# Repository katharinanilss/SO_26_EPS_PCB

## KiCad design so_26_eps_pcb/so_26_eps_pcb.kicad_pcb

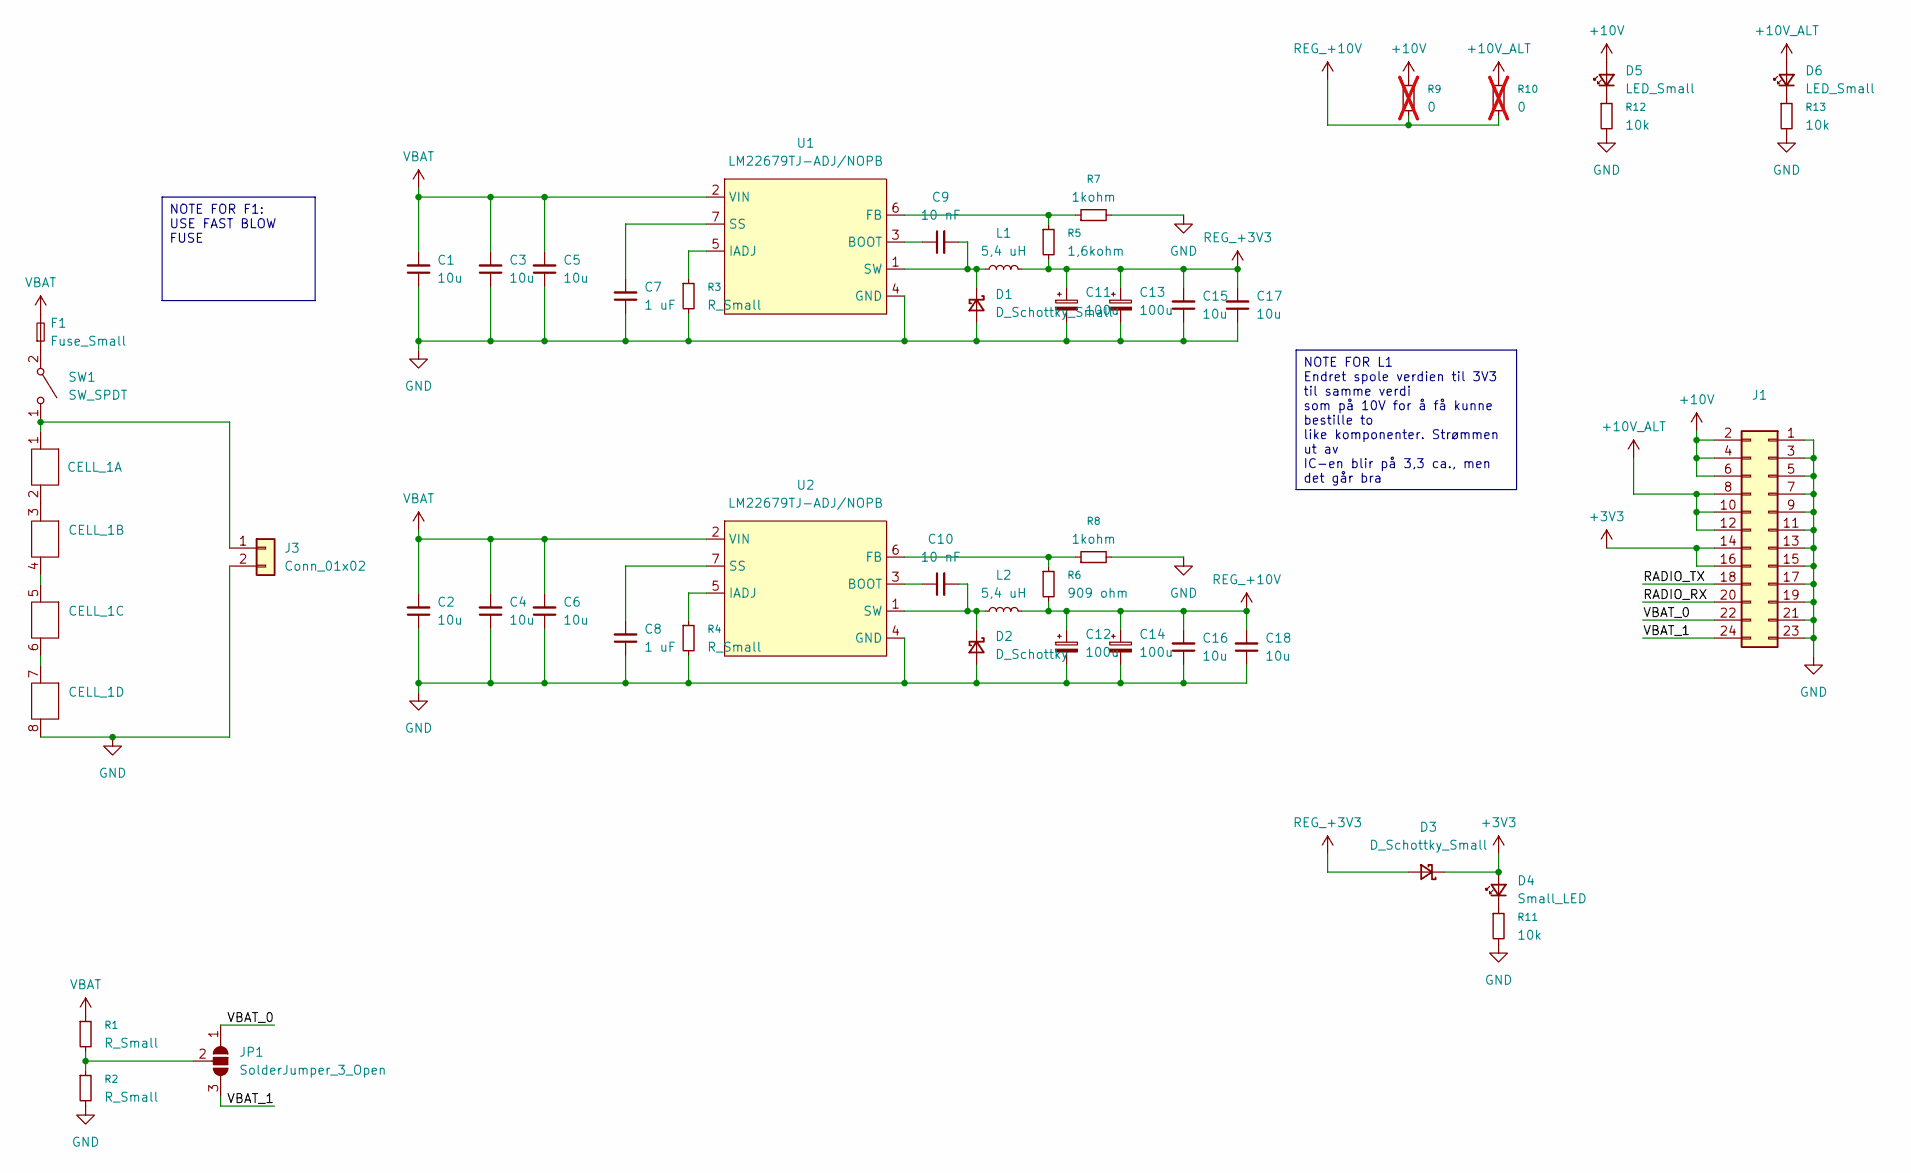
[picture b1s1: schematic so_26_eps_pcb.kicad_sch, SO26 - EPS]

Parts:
C1, C2, C3, C4, C5, C6, C15, C16, C17, C18: 10u; C_1206_3216Metric_Pad1.33x1.80mm_HandSolder
C7, C8: 1 uF; C_1206_3216Metric_Pad1.33x1.80mm_HandSolder
C9, C10: 10 nF; C_0805_2012Metric_Pad1.18x1.45mm_HandSolder
C11, C12, C13, C14: 100u; CP_Radial_D6.3mm_P2.50mm
CELL_1: Battery holder
D1, D3: D_Schottky_Small; D_SOD-128
D2: D_Schottky; D_SOD-128
D4: Small_LED; LED_0805_2012Metric_Pad1.15x1.40mm_HandSolder
D5, D6: LED_Small; LED_0805_2012Metric_Pad1.15x1.40mm_HandSolder
F1: Fuse_Small; Surface Mount Fuse Block
J1: Conn_02x12_Odd_Even; PinSocket_2x12_P2.54mm_Vertical
J3: Conn_01x02; 01x02_header
JP1: SolderJumper_3_Open; SolderJumper-3_P2.0mm_Open_TrianglePad1.0x1.5mm_NumberLabels
L1, L2: 5,4 uH; SRU1048 Inductor
R1, R2, R3, R4: R_Small; R_0805_2012Metric_Pad1.20x1.40mm_HandSolder
R5: 1,6kohm; R_0805_2012Metric_Pad1.20x1.40mm_HandSolder
R6: 909 ohm; R_0805_2012Metric_Pad1.20x1.40mm_HandSolder
R7, R8: 1kohm; R_0805_2012Metric_Pad1.20x1.40mm_HandSolder
R9, R10: 0; R_2512_6332Metric_Pad1.40x3.35mm_HandSolder; not fitted
R11, R12, R13: 10k; R_0805_2012Metric_Pad1.20x1.40mm_HandSolder
SW1: SW_SPDT; finalswitchfinal
U1, U2: LM22679TJ-ADJ/NOPB; TO-263-7_TabPin4

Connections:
+3V3: D3.1 (K), D4.2 (A), J1.14, J1.16
+10V: D5.2 (A), J1.2, J1.4, J1.6, R9.1
+10V_ALT: D6.2 (A), J1.8, J1.10, J1.12, R10.1
/RADIO_RX: J1.20
/RADIO_TX: J1.18
/VBAT_0: J1.22, JP1.1 (A)
/VBAT_1: J1.24, JP1.3 (B)
GND: C1.1, C2.1, C3.1, C4.1, C5.1, C6.1, C7.1, C8.1, C11.2, C12.2, C13.2, C14.2, C15.1, C16.1, C17.1, C18.1, CELL_1.8, D1.2 (A), D2.2 (A), J1.1, J1.3, J1.5, J1.7, J1.9, J1.11, J1.13, J1.15, J1.17, J1.19, J1.21, J1.23, J3.2, R2.2, R3.2, R4.2, R7.2, R8.2, R11.2, R12.2, R13.2, U1.4 (GND), U2.4 (GND)
unnamed: CELL_1.2, CELL_1.3
unnamed: CELL_1.4, CELL_1.5
unnamed: CELL_1.6, CELL_1.7
unnamed: C9.2, D1.1 (K), L1.1, U1.1 (SW)
unnamed: C10.2, D2.1 (K), L2.1, U2.1 (SW)
unnamed: D4.1 (K), R11.1
unnamed: D5.1 (K), R12.1
unnamed: D6.1 (K), R13.1
unnamed: CELL_1.1, J3.1, SW1.1 (A)
unnamed: JP1.2 (C), R1.2, R2.1
unnamed 18: F1.1, SW1.2 (B); also elsewhere on the board
unnamed: C9.1, U1.3 (BOOT)
unnamed: R5.1, R7.1, U1.6 (FB)
unnamed: R3.1, U1.5 (IADJ)
unnamed: C7.2, U1.7 (SS)
unnamed: C10.1, U2.3 (BOOT)
unnamed: R6.1, R8.1, U2.6 (FB)
unnamed: R4.1, U2.5 (IADJ)
unnamed: C8.2, U2.7 (SS)
REG_+3V3: C11.1, C13.1, C15.2, C17.2, D3.2 (A), L1.2, R5.2
REG_+10V: C12.1, C14.1, C16.2, C18.2, L2.2, R6.2, R9.2, R10.2
VBAT: C1.2, C2.2, C3.2, C4.2, C5.2, C6.2, F1.2, R1.1, U1.2 (VIN), U2.2 (VIN); also elsewhere on the board

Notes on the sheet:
NOTE FOR F1: USE FAST BLOW FUSE
NOTE FOR L1 Endret spole verdien til 3V3 til samme verdi som på 10V for å få kunne bestille to like komponenter. Strømmen ut av IC-en blir på 3,3 ca., men det går bra

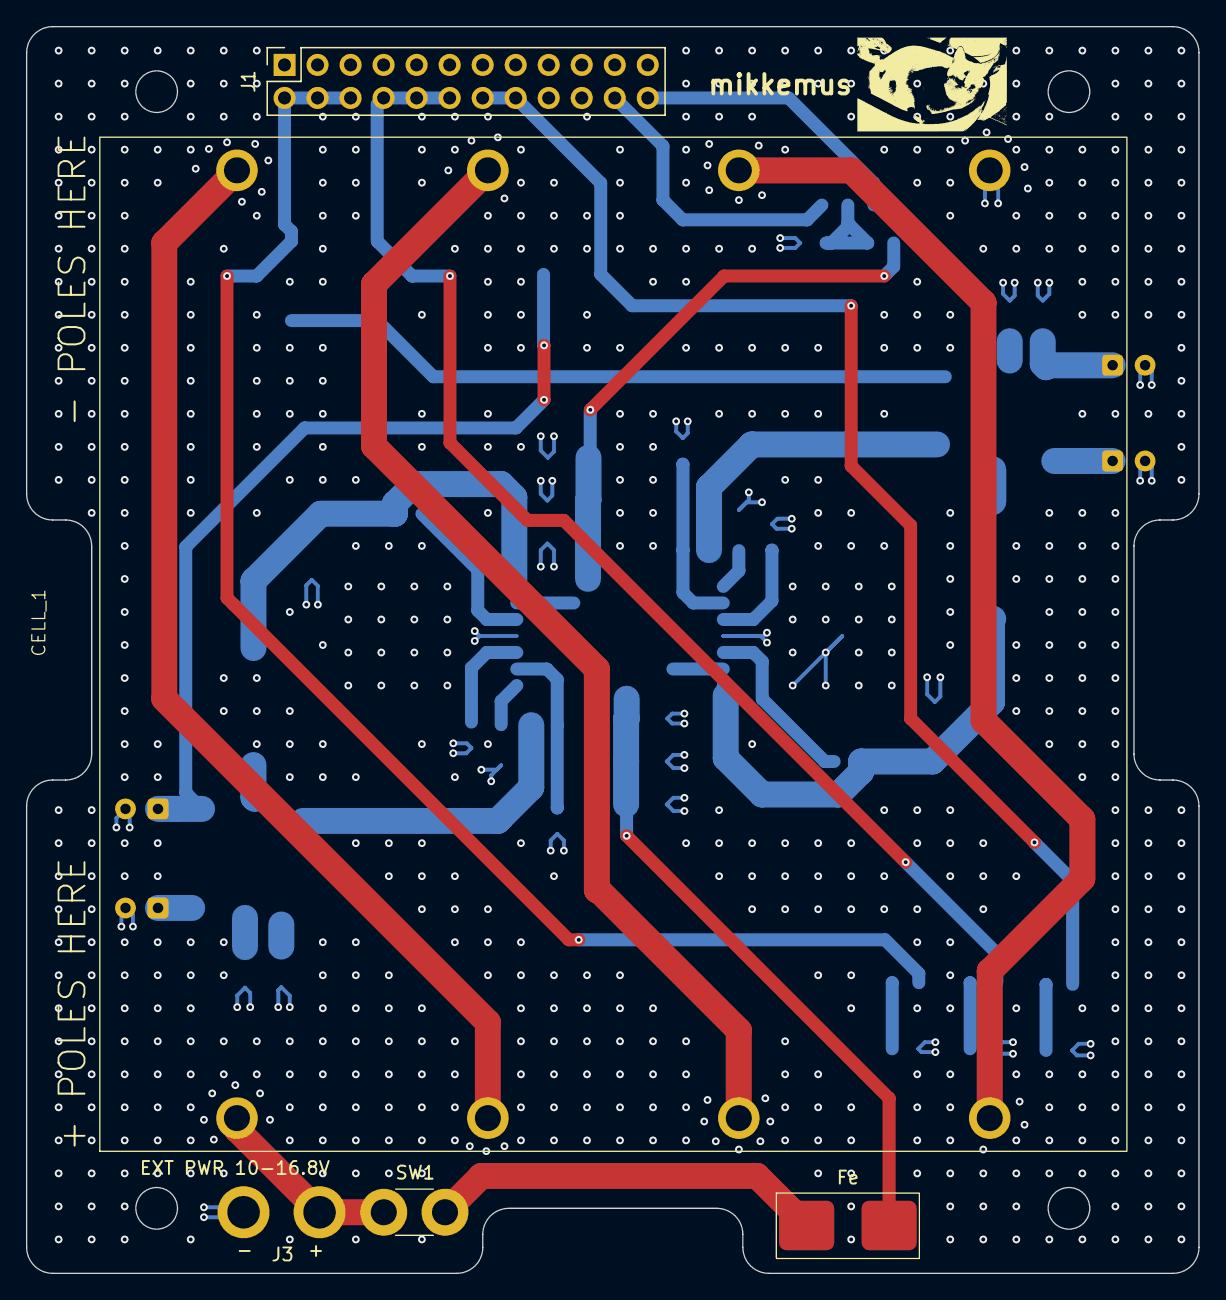
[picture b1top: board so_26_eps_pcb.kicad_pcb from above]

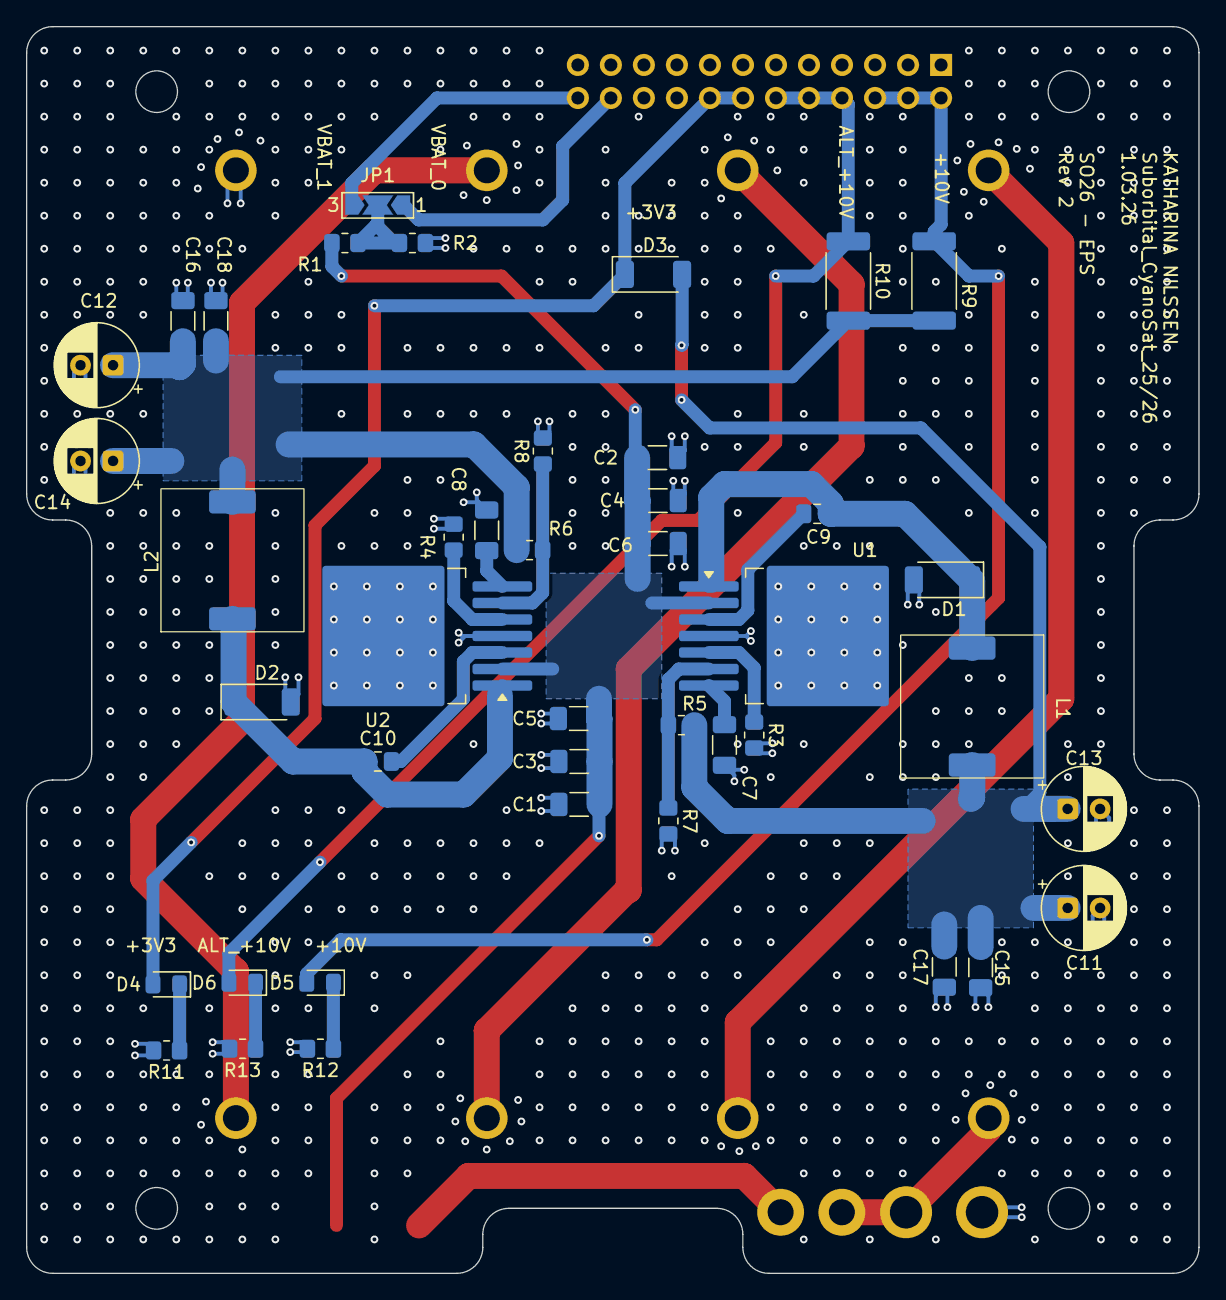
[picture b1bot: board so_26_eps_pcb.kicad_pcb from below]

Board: 4 copper layers, 90.2 x 95.9 mm, 48 parts (42 on the bottom side), 28 nets.

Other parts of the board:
Fe: Fuse_Small; Surface Mount Fuse Block
mikkemus: LOGO

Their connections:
unnamed 18: Fe.1; also elsewhere on the board
VBAT: Fe.2; also elsewhere on the board

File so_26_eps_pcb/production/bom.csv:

Designator,Footprint,Quantity,Value,LCSC Part #
18650 BATTERY HOLDER,Battery holder,1,~,
"C1, C15, C16, C17, C18, C2, C3, C4, C5, C6",1206,10,10u,
"C10, C9",0805,2,10 nF,
"C11, C12, C13, C14",CP_Radial_D6.3mm_P2.50mm,4,100u,
"C7, C8",1206,2,1 uF,
"D1, D3",D_SOD-128,2,D_Schottky_Small,
D2,D_SOD-128,1,D_Schottky,
D4,0805,1,Small_LED,
"D5, D6",0805,2,LED_Small,
F1,Surface Mount Fuse Block,1,Fuse_Small,
J1,PinSocket_2x12_P2.54mm_Vertical,1,Conn_02x12_Odd_Even,
J3,01x02_header,1,Conn_01x02,
"L1, L2",SRU1048 Inductor,2,"5,4 uH",
"R1, R2, R3, R4",0805,4,R_Small,
"R10, R9",2512,2,0,
"R11, R12, R13",0805,3,10k,
R5,0805,1,"1,6kohm",
R6,0805,1,909 ohm,
"R7, R8",0805,2,1kohm,
SW1,PinSocket_1x02_P2.54mm_Vertical,1,SW_SPDT,
"U1, U2",TO-263-7_TabPin4,2,LM22679TJ-ADJ/NOPB,

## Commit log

2026-01-28 init commit
2026-01-28 schematic: updated title block
2026-02-06 Laget symbol for LM22679TJ-ADJ/NOPB
    Laget symbol for LM22679TJ-ADJ/NOPB
2026-02-06 Laget ferdig regulatorer
    Mangler noen verdier
2026-02-06 Battery
    Yuhhh
2026-02-06 Battery symbol
    I have made one symbol, battery, that contains 4 different units which represent the 4 batteries in one battery holder
2026-02-06 Finished
    The circuit design are finished!!!
2026-02-08 checked by aj
    schematic
    - fixed symbols and added capacitors
    pcb
    - added outline and stack + some footprints
2026-02-08 backup
2026-02-08 Made footprints
2026-02-08 Added test points
2026-02-08 Changed properties for L
2026-02-08 Made a new battery holder
    Lets hope this one doesn’t get an error!
2026-02-08 Changed battery cells
    Gave input and outputs their own number
2026-02-08 Made battery holder footprint
2026-02-08 Added the last footprints
2026-02-08 Edits on PCB editor
2026-02-08 Last info about footprints
2026-02-08 Updated some settings
2026-02-08 ogabog
2026-02-09 Updated some footprints
    Deleted some old components and changed the size on the testpoints from 2mm in diameters to 1.5mm in diameters
2026-02-09 Made footprints for header by switch
2026-02-09 Added two headers to the system
2026-02-09 pcb
    placed components close to each other to get an visual of the space
2026-02-09 Saved the pcb file
2026-02-10 Changed header footprint
    changed the header footprint, but it won’t update in the pcb editor
2026-02-10 Rev 1 of placing components on pcb
2026-02-10 Changed the place on some of the components on the PCB
2026-02-10 Saved the pcb
2026-02-10 Started some rooting
2026-02-10 Finished rooting the positive parts
2026-02-11 Saved
    some changes needs to be done on the wires
2026-02-11 Changed the thickness on some wires
2026-02-11 Saved
2026-02-11 REV 1 FINAL
    SHEMATIC AND PCB CHECK
    DRC/ERC PASSED
2026-02-11 added via stiching
2026-02-11 added text "ext pwr 10-16.8v"
2026-02-11 added rev 1 text
2026-02-12 added text
2026-02-15 Looked at changes
2026-02-22 rev 2 beginning
2026-02-22 Placed components for 10V
    Also made a filled zone for VBAT
2026-02-22 Placed VBAT components and wiring
2026-02-22 Saved the work
2026-02-24 Tried to make a design of the 10V reg and started on the 3V3 reg
2026-02-24 Started the 3V3 reg
2026-02-25 Finished the 3V3 reg
2026-02-25 Uptaded switch footprints
2026-03-01 Saved document
2026-03-01 Traced and placed the last components
2026-03-01 Made some last changes to the tracing
2026-03-01 Feel like i finshed
2026-03-01 Added an image
2026-03-01 changed the image a bit
2026-03-01 last changes
2026-03-01 saved changes
2026-03-08 nothing done
